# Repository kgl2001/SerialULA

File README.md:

# Acorn BBC Micro Serial ULA Replacement
This module designed as a drop in replacement for the Serial Interface IC, 2C199 (IC7) on the BBC Micro.

Some general notes:

* The source files are to be used with KiCAD v9.0.0 or later.
* The gerber files have been optimised for fabrication by JLCPCB. In particular, there is a 8mmx8mm silkscreen box on the rear of the PCB. This is to allow a 2D barcode, with unique serial number to be printed on the PCB.
* If you want the barcode to be added, then make sure to select this option in the 'Mark on PCB' field, and make sure to select 'Specify position' in the '2D Barcode Position' field, otherwise you will end up with a white 8mm x 8mm box printed on your PCB and a 8mm x 8mm barcode printed at a position of JLCPCBs choosing. Thrust me on this!
* If you don't want the barcode added, then remove the 8mm x 8mm box from the silkscreen layer and regenerate the gerbers. Otherwise you will end up with a white 8mm x 8mm box printed on your PCB.
* A combined CPL / BOM file is included in the gerber directory. Again, this is for use with JLCPCB, if you want to use their PCBA (PCB Assembly) to solder on all the SMD parts.
* The CPL / BOM file includes two different options for LDO regulator and associated capacitors. Select one set only - either U2, C2.1 & C2.2 OR U3, C4 & C5. If using JLCPCB for assembly, you can deselect one set during the PCBA ordering process.
* You will need to source suitable round pin headers, and solder these onto the underside of the PCB. These headers will then plug into IC socket 7 on the beeb motherboard.

Please refer to the following discussion on Stardot for further details: https://stardot.org.uk/forums/viewtopic.php?t=30963

## Schematic

## Author

The Serial ULA Replacement module is developed and maintained by Ken Lowe.
    
## Hardware License (Creative Commons BY-SA 4.0)

Please see the following link for details: https://creativecommons.org/licenses/by-sa/4.0/

You are free to:

Share - copy and redistribute the material in any medium or format
Adapt - remix, transform, and build upon the material
for any purpose, even commercially.

This license is acceptable for Free Cultural Works.

The licensor cannot revoke these freedoms as long as you follow the license terms.

Under the following terms:

Attribution - You must give appropriate credit, provide a link to the license, and indicate if changes were made. You may do so in any reasonable manner, but not in any way that suggests the licensor endorses you or your use.

ShareAlike - If you remix, transform, or build upon the material, you must distribute your contributions under the same license as the original.

No additional restrictions - You may not apply legal terms or technological measures that legally restrict others from doing anything the license permits.

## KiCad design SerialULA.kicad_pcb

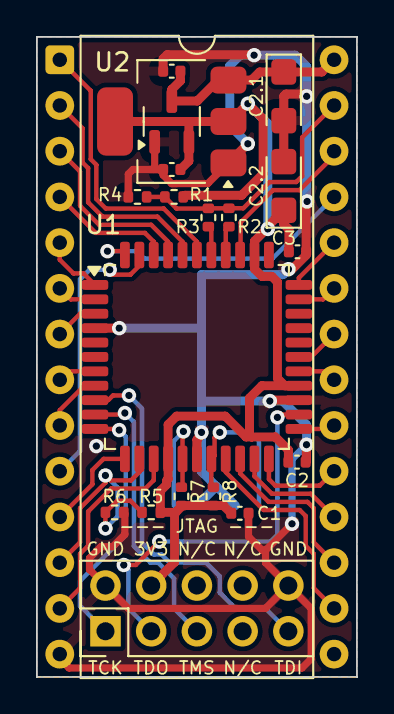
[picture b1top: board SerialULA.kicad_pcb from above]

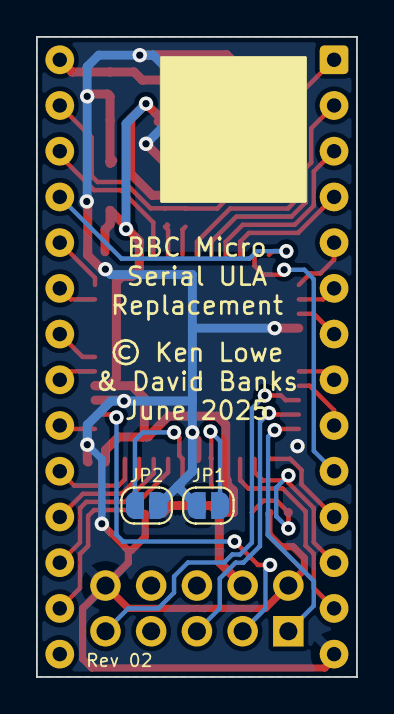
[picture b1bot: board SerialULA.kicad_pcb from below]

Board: 2 copper layers, 17.8 x 35.6 mm, 22 parts (2 on the bottom side), 36 nets.

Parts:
C1, C2, C3: 100n; C_0402_1005Metric
C2.1, C2.2: 10uF; CP_EIA-3216-18_Kemet-A
C4, C5: 1u; C_0402_1005Metric
J1: JTAG-IDC; PinHeader_2x05_P2.54mm_Vertical
JP1, JP2: SolderJumper_2_Open; SolderJumper-2_P1.3mm_Open_RoundedPad1.0x1.5mm
R1, R4: 2K0; R_0402_1005Metric
R2: 1K8; R_0402_1005Metric
R3, R6: 1K0; R_0402_1005Metric
R5: 1K2; R_0402_1005Metric
R7, R8: 10K; R_0402_1005Metric
U1: XC9572XL-10VQG44C; LQFP-44_10x10mm_P0.8mm
U2: AMS1117-3.3; SOT-223-3_TabPin2
U3: XC6206P332MR; SOT-23-3
U4: 2C199; DIP-28_W15.24mm

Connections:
+3.3V: C1.1, C2.1, C2.2.1, C3.1, C5.1, J1.4, R1.1, R5.1, R7.2, R8.2, U1.15 (VCC), U1.26 (VCCIO), U1.35 (VCC), U2.2 (VO), U3.2 (VO)
+5V: C2.1.1, C4.1, U2.3 (VI), U3.3 (VI), U4.28 (VCC)
/CTSI: U1.23, U4.20 (CTSI)
/CTSO: U1.22, U4.19 (CTSO)
/CasIn: R5.2, R6.1, U1.13, U4.12 (CasIn)
/CasMotor: U1.12, U4.11 (CasMotor)
/CasOut: R1.2, R2.1, R3.1, R4.1, U4.27 (CasOut)
/CasOut0: R3.2, U1.38
/CasOut1: R2.2, U1.37
/Clk: U1.44 (I/O/GCK2), U4.25 (Clk)
/D0: U1.39, U4.1 (D0)
/D1: U1.40, U4.2 (D1)
/D2: U1.41, U4.3 (D2)
/D3: U1.42, U4.4 (D3)
/D4: U1.1 (I/O/GCK3), U4.5 (D4)
/D5: U1.2, U4.6 (D5)
/D6: U1.3, U4.7 (D6)
/D7: U1.7, U4.8 (D7)
/DCD: U1.14, U4.13 (DCD)
/Din: U1.19, U4.16 (Din)
/Dout: U1.27, U4.21 (Dout)
/E: U1.43 (I/O/GCK1), U4.10 (E)
/RTSI: U1.33 (I/O/GSR), U4.24 (RTSI)
/RTSO: U1.32, U4.23 (RTSO)
/RxC: U1.21, U4.18 (RxC)
/RxD: U1.20, U4.17 (RxD)
/TCK: J1.1, U1.11 (TCK)
/TDI: J1.9, U1.9 (TDI)
/TDO: J1.3, U1.24 (TDO)
/TMS: J1.5, U1.10 (TMS)
/TxC: U1.36 (I/O/GTS1), U4.26 (TxC)
/TxD: U1.28, U4.22 (TxD)
/~CS: U1.8, U4.9 (~CS)
GND: C1.2, C2.2, C2.1.2, C2.2.2, C3.2, C4.2, C5.2, J1.2, J1.10, JP1.1 (A), JP2.1 (A), R4.2, R6.2, U1.4 (GND), U1.17 (GND), U1.25 (GND), U2.1 (GND), U3.1 (GND), U4.14 (GND)
unnamed: JP1.2 (B), R7.1, U1.16
unnamed: JP2.2 (B), R8.1, U1.18

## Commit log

2025-05-01 Add License
2025-05-01 Add ReadMe
2025-05-01 Fix link
2025-06-22 Initial commit of Rev 02 hardware
    - Dual footprint for both large and small LDO regulator / capacitors.
    - Updated resistor values at R1, R2, R3 & R4 for CasOutX. Now pulling up to 3.3V instead of 5V
    - Connected extra solder bridge with pull up into spare CPLD input for possible future 'extended features'.
2025-06-22 Delete SerialULA.drl
    File relocated to Gerbers directory
2025-07-09 Fix BOM / CPL xlsx file
    Also add tab delimited version
2026-03-05 Revert commit 2e120ae
    Restore original Rev 01 CPL / BOM file
2026-03-05 Revert commit 2e120ae
    Delete Gerbers/SerialULA-BOM_CPL.txt
2026-03-05 Fix BOM / CPL file
    Fix SerialULA-BOM_CPL.xlsx file
    Add SerialULA-BOM_CPL.txt file
2026-03-05 Update README.md
    Add schematic

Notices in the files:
SerialULA.kicad_pcb:
© Ken Lowe
